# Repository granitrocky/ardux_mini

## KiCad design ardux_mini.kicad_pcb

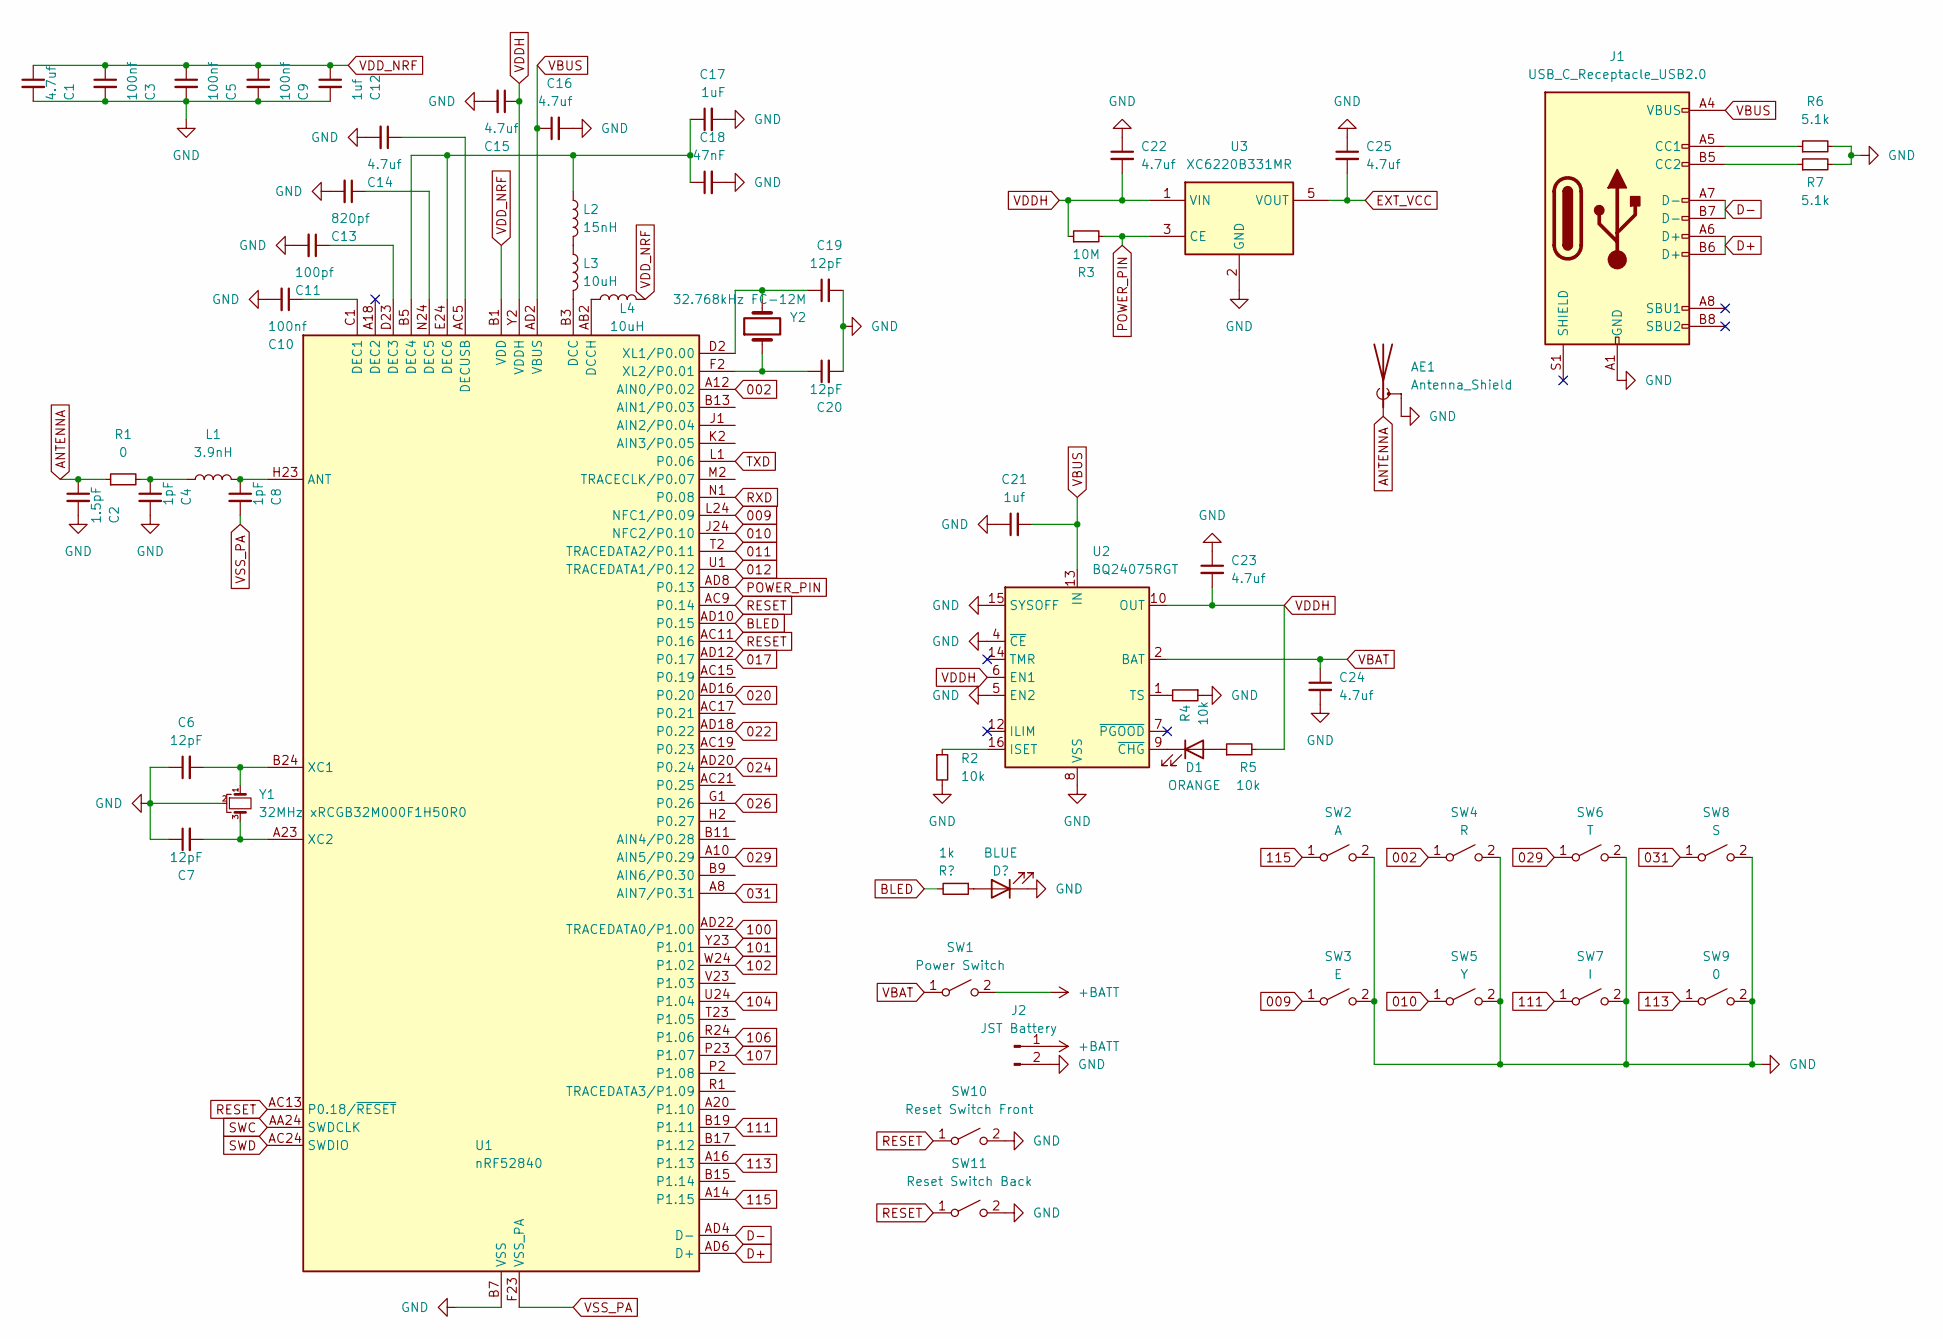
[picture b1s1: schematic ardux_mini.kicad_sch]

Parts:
AE1: Antenna_Shield; SWRA117D
C1, C14, C15, C16, C22, C23, C24, C25: 4.7uf; C_0402_1005Metric
C2: 1.5pF; C_0402_1005Metric
C3, C5, C9, C10: 100nf; C_0402_1005Metric
C4, C8: 1pF; C_0402_1005Metric
C6, C7, C19, C20: 12pF; C_0402_1005Metric
C11: 100pf; C_0402_1005Metric
C12, C21: 1uf; C_0402_1005Metric
C13: 820pf; C_0402_1005Metric
C17: 1uF; C_0402_1005Metric
C18: 47nF; C_0402_1005Metric
D1: ORANGE; LED_0603_1608Metric
J1: USB_C_Receptacle_USB2.0; USB_C_Receptacle_HRO_TYPE-C-31-M-12
J2: JST Battery; JST_EH_S2B-EH_1x02_P2.50mm_Horizontal
L1: 3.9nH; L_0402_1005Metric
L2: 15nH; L_0402_1005Metric
L3, L4: 10uH; L_0805_2012Metric
R1: 0; R_0402_1005Metric
R2, R4, R5: 10k; R_0402_1005Metric
R3: 10M; R_0402_1005Metric
R6, R7: 5.1k; R_0402_1005Metric
SW1: Power Switch; switch_MSK-12C02_smd
SW2: A; CherryMX_Choc_1u_reversible
SW3: E; CherryMX_Choc_1u_reversible
SW4: R; CherryMX_Choc_1u_reversible
SW5: Y; CherryMX_Choc_1u_reversible
SW6: T; CherryMX_Choc_1u_reversible
SW7: I; CherryMX_Choc_1u_reversible
SW8: S; CherryMX_Choc_1u_reversible
SW9: 0; CherryMX_Choc_1u_reversible
SW10: Reset Switch Front; SW_SPST_TL3342
SW11: Reset Switch Back; SW_SPST_TL3342
U1: nRF52840; Nordic_AQFN-73-1EP_7x7mm_P0.5mm
U2: BQ24075RGT; VQFN-16-1EP_3x3mm_P0.5mm_EP1.6x1.6mm
U3: XC6220B331MR; SOT-23-5
Y1: 32MHz xRCGB32M000F1H50R0; OSC_XRCGB32M000F1H50R0
Y2: 32.768kHz FC-12M; FC-12M 32.7680KA-A3

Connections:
002: SW4.1 (A), U1.A12 (AIN0/P0.02)
009: SW3.1 (A), U1.L24 (NFC1/P0.09)
010: SW5.1 (A), U1.J24 (NFC2/P0.10)
011: U1.T2 (TRACEDATA2/P0.11)
012: U1.U1 (TRACEDATA1/P0.12)
017: U1.AD12 (P0.17)
020: U1.AD16 (P0.20)
022: U1.AD18 (P0.22)
024: U1.AD20 (P0.24)
026: U1.G1 (P0.26)
029: SW6.1 (A), U1.A10 (AIN5/P0.29)
031: SW8.1 (A), U1.A8 (AIN7/P0.31)
100: U1.AD22 (TRACEDATA0/P1.00)
101: U1.Y23 (P1.01)
102: U1.W24 (P1.02)
104: U1.U24 (P1.04)
106: U1.R24 (P1.06)
107: U1.P23 (P1.07)
111: SW7.1 (A), U1.B19 (P1.11)
113: SW9.1 (A), U1.A16 (P1.13)
115: SW2.1 (A), U1.A14 (P1.15)
+BATT: J2.1, SW1.2 (B)
ANTENNA: AE1.1 (A), C2.1, R1.1
BLED: U1.AD10 (P0.15); also elsewhere on the board
D+: J1.A6 (D+), J1.B6 (D+), U1.AD6 (D+)
D-: J1.A7 (D-), J1.B7 (D-), U1.AD4 (D-)
EXT_VCC: C25.2, U3.5 (VOUT)
GND: AE1.2 (Shield), C1.2, C2.2, C3.2, C4.2, C5.2, C6.1, C7.1, C9.2, C10.2, C11.2, C12.2, C13.2, C14.2, C15.2, C16.2, C17.2, C18.2, C19.2, C20.2, C21.1, C22.1, C23.1, C24.2, C25.1, J1.A1 (GND), J1.A12 (GND), J1.B1 (GND), J1.B12 (GND), J2.2, R2.2, R4.1, R6.2, R7.2, SW2.2 (B), SW3.2 (B), SW4.2 (B), SW5.2 (B), SW6.2 (B), SW7.2 (B), SW8.2 (B), SW9.2 (B), SW10.2 (B), SW11.2 (B), U1.B7 (VSS), U1.EP (VSS), U2.4 (~CE), U2.5 (EN2), U2.8 (VSS), U2.15 (SYSOFF), U2.17 (VSS), U3.2 (GND), Y1.2; also elsewhere on the board
unnamed: C4.1, L1.1, R1.2
unnamed: C6.2, U1.B24 (XC1), Y1.1
unnamed: C7.2, U1.A23 (XC2), Y1.3
unnamed: C8.1, L1.2, U1.H23 (ANT)
unnamed: C10.1, U1.C1 (DEC1)
unnamed: C11.1, U1.D23 (DEC3)
unnamed: C13.1, U1.N24 (DEC5)
unnamed: C14.1, U1.AC5 (DECUSB)
unnamed: C17.1, C18.1, L2.1, U1.B5 (DEC4), U1.E24 (DEC6)
unnamed: C19.1, U1.D2 (XL1/P0.00), Y2.2
unnamed: C20.1, U1.F2 (XL2/P0.01), Y2.1
unnamed: D1.1 (K), U2.9 (~CHG)
unnamed: D1.2 (A), R5.1
unnamed: J1.A5 (CC1), R6.1
unnamed: J1.B5 (CC2), R7.1
unnamed: L2.2, L3.1
unnamed: L3.2, U1.B3 (DCC)
unnamed: R2.1, U2.16 (ISET)
unnamed: R4.2, U2.1 (TS)
unnamed: L4.1, U1.AB2 (DCCH)
POWER_PIN: R3.2, U1.AD8 (P0.13), U3.3 (CE)
RESET: SW10.1 (A), SW11.1 (A), U1.AC9 (P0.14), U1.AC11 (P0.16), U1.AC13 (P0.18/~RESET)
RXD: U1.N1 (P0.08)
SWC: U1.AA24 (SWDCLK); also elsewhere on the board
SWD: U1.AC24 (SWDIO); also elsewhere on the board
TXD: U1.L1 (P0.06)
VBAT: C24.1, SW1.1 (A), U2.2 (BAT), U2.3 (BAT)
VBUS: C16.1, C21.2, J1.A4 (VBUS), J1.A9 (VBUS), J1.B4 (VBUS), J1.B9 (VBUS), U1.AD2 (VBUS), U2.13 (IN)
VDDH: C15.1, C22.2, C23.2, R3.1, R5.2, U1.Y2 (VDDH), U2.6 (EN1), U2.10 (OUT), U2.11 (OUT), U3.1 (VIN)
VDD_NRF: C1.1, C3.1, C5.1, C9.1, C12.1, L4.2, U1.A22 (VDD), U1.AD14 (VDD), U1.AD23 (VDD), U1.B1 (VDD), U1.W1 (VDD)
VSS_PA: C8.2, U1.F23 (VSS_PA)

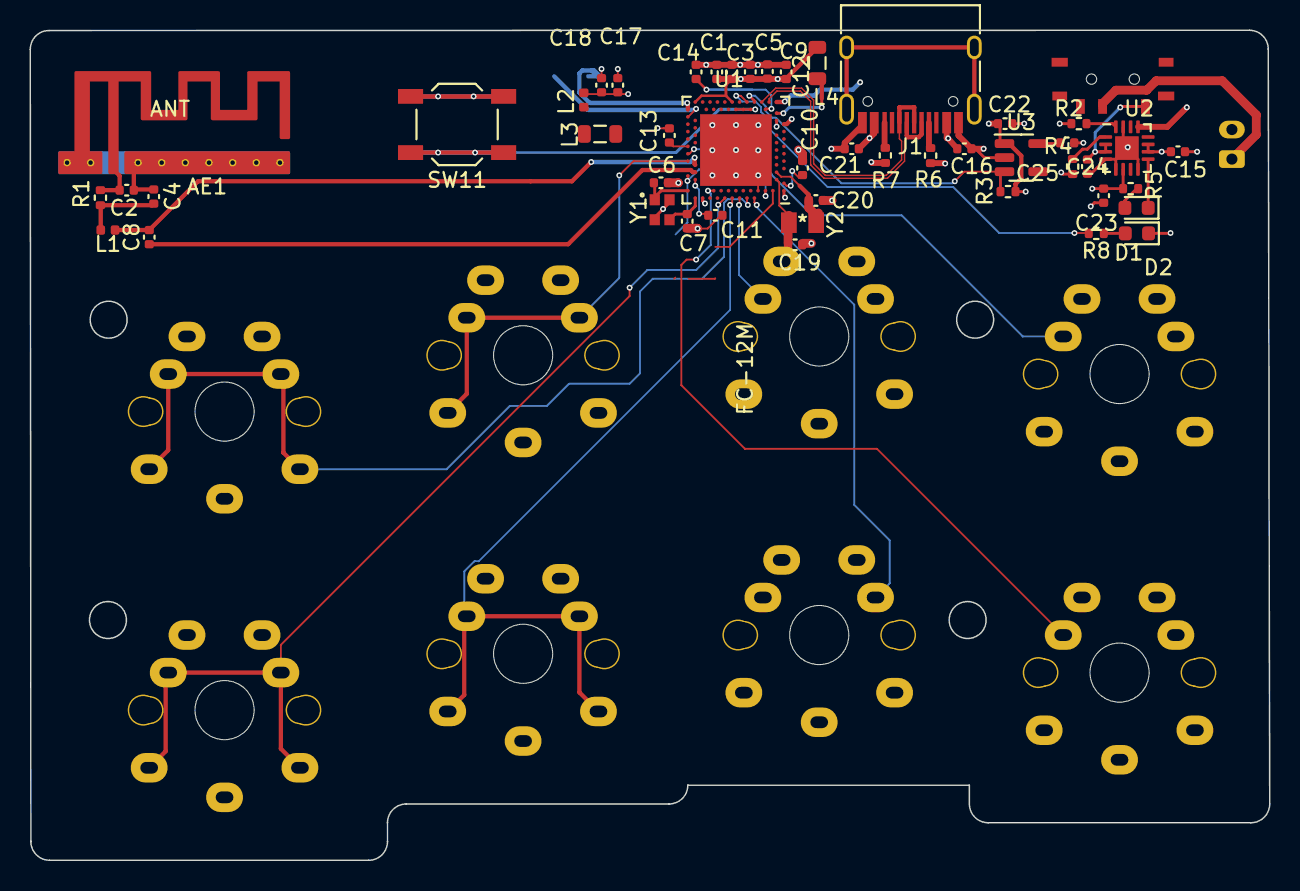
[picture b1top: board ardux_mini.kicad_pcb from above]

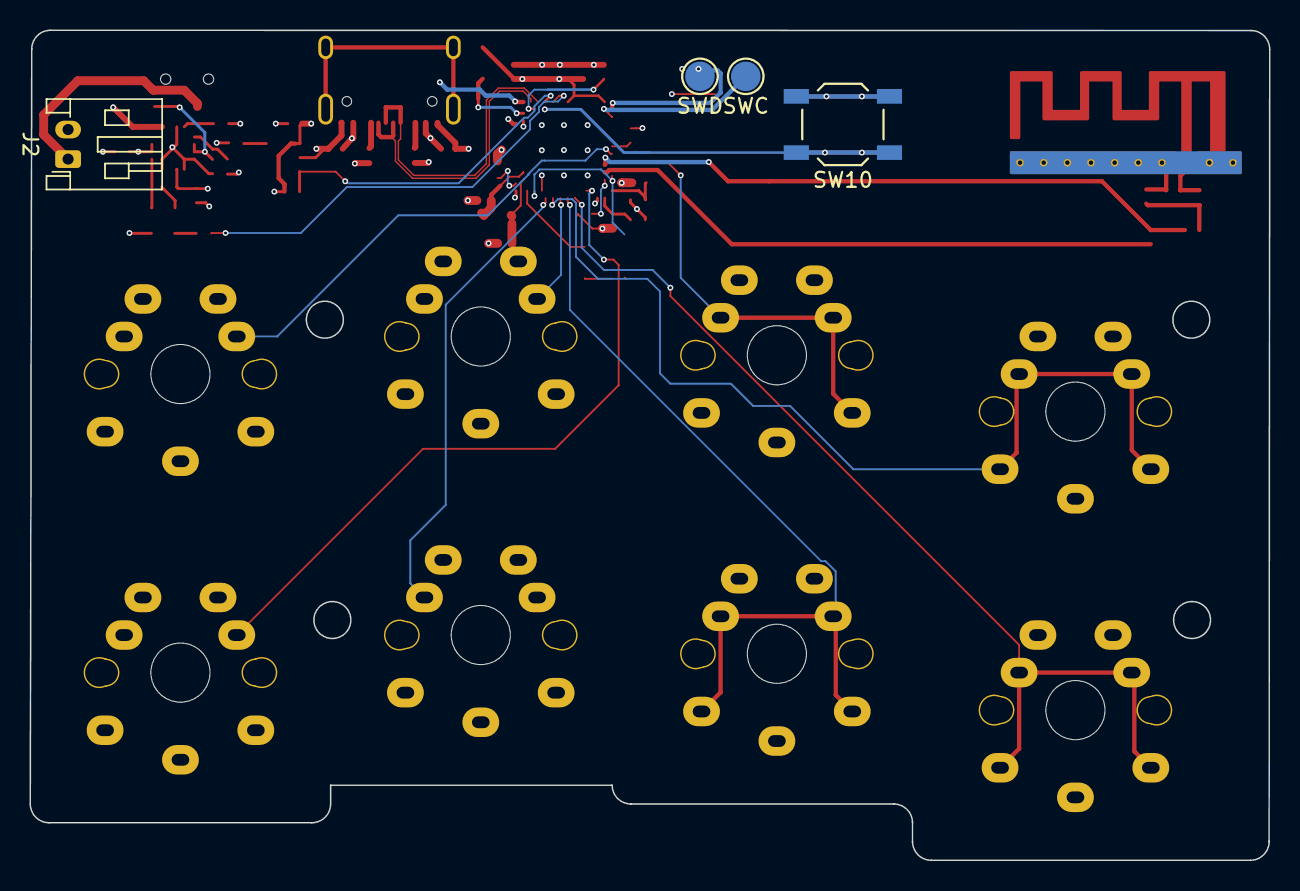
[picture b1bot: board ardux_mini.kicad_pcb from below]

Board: 4 copper layers, 83.9 x 56.2 mm, 60 parts (4 on the bottom side), 45 nets.

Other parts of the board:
D2: BLUE; LED_0603_1608Metric
R8: 1k; R_0402_1005Metric
SWC: TestPoint_Pad_D2.0mm
SWD: TestPoint_Pad_D2.0mm

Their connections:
BLED: R8.2; also elsewhere on the board
GND: D2.1 (K); also elsewhere on the board
unnamed: D2.2 (A), R8.1
SWC: SWC.1; also elsewhere on the board
SWD: SWD.1; also elsewhere on the board

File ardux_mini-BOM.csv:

Comment,Designator,Footprint,LCSC Part Number
100pf,C11,C_0402_1005Metric,C1546
1uf,"C12,C21",C_0402_1005Metric,C52923
820pf,C13,C_0402_1005Metric,C1543
4.7uf,"C14,C22,C1,C15,C16,C25,C23,C24",C_0402_1005Metric,C23733
1uF,C17,C_0402_1005Metric,C52923
47nF,C18,C_0402_1005Metric,C272875
1.5pF,C2,C_0402_1005Metric,C1552
12pF,"C20,C7,C6,C19",C_0402_1005Metric,C1547
100nf,"C5,C9,C3,C10",C_0402_1005Metric,C307331
1pF,"C8,C4",C_0402_1005Metric,C1550
ORANGE,D1,LED_0603_1608Metric,C434425
BLUE,D2,LED_0603_1608Metric,C72041
USB_C_Receptacle_USB2.0,J1,USB_C_Receptacle_HRO_TYPE-C-31-M-12,C165948
JST Battery,J2,JST_PH_S2B-PH-K_1x02_P2.00mm_Horizontal,
3.9nH,L1,L_0402_1005Metric,C14033
15nH,L2,L_0402_1005Metric,C27143
10uH,"L4,L3",L_0805_2012Metric,C1046
0,R1,R_0402_1005Metric,C25756
10k,"R2,R5,R4",R_0402_1005Metric,C25744
10M,R3,R_0402_1005Metric,C26082
5.1k,"R7,R6",R_0402_1005Metric,C25905
1k,R8,R_0402_1005Metric,C11702
Power Switch,SW1,switch_MSK-12C02_smd,C431541
Reset Switch Front,SW10,SW_SPST_TL3342,C2886894
Reset Switch Back,SW11,SW_SPST_TL3342,
nRF52840,U1,Nordic_AQFN-73-1EP_7x7mm_P0.5mm,C190794
BQ24075RGT,U2,VQFN-16-1EP_3x3mm_P0.5mm_EP1.6x1.6mm,C15464
XC6220B331MR,U3,SOT-23-5,C86534
32MHz xRCGB32M000F1H50R0,Y1,OSC_XRCGB32M000F1H50R0,C880116
 FC-12M,Y2,FC-12M 32.7680KA-A3,C99009

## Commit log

2022-10-21 Initial Revision. Technically Rev0.2, but we don't talk about Rev0.1
